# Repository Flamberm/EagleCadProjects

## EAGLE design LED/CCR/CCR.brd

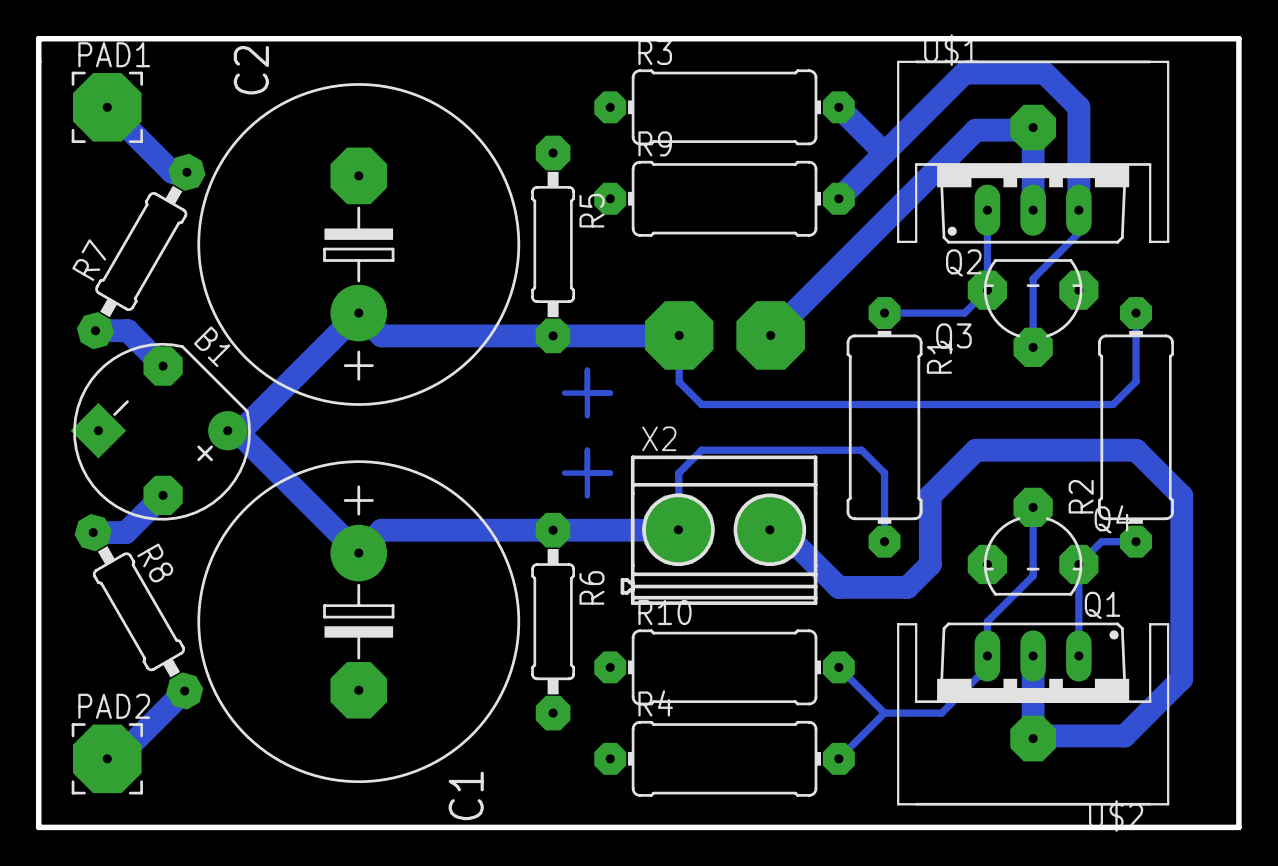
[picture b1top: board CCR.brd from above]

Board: 2 copper layers, 66.7 x 43.8 mm, 23 parts (1 on the bottom side), 12 nets.

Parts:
B1: RB1A
C1, C2: E7,5-18
PAD1, PAD2: 3,81/1,4
Q1, Q2: BUZ11BV; TO220BV
Q3, Q4: KSP42TA; SOT-92WIDE
R1, R2: 300k; 0411/12
R3, R4: 13R; 0411/12
R5, R6: 160k; 0207/10
R7, R8: NTC; 0207/10
R9, R10: 8R2; 0411/12
U$1, U$2: SK95-3M3
X1, X2: MKDSN1,5/2-5,08

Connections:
GND: B1.-, C1.-, C2.-, Q3.E, Q4.E, R3.1, R4.1, R5.1, R6.2, R9.1, R10.1
unnamed: Q1.S, Q4.B, R4.2, R10.2
unnamed: Q1.D, U$2.P$1, X2.2
unnamed: Q2.D, U$1.P$1, X1.1
unnamed: Q2.S, Q3.B, R3.2, R9.2
unnamed: Q1.G, Q4.C, R2.1
unnamed: Q2.G, Q3.C, R1.1
unnamed: PAD1.1, R7.2
unnamed: B1.AC1, R8.1
unnamed: PAD2.1, R8.2
unnamed: B1.AC2, R7.1
unnamed: B1.+, C1.+, C2.+, R1.2, R2.2, R5.2, R6.1, X1.2, X2.1

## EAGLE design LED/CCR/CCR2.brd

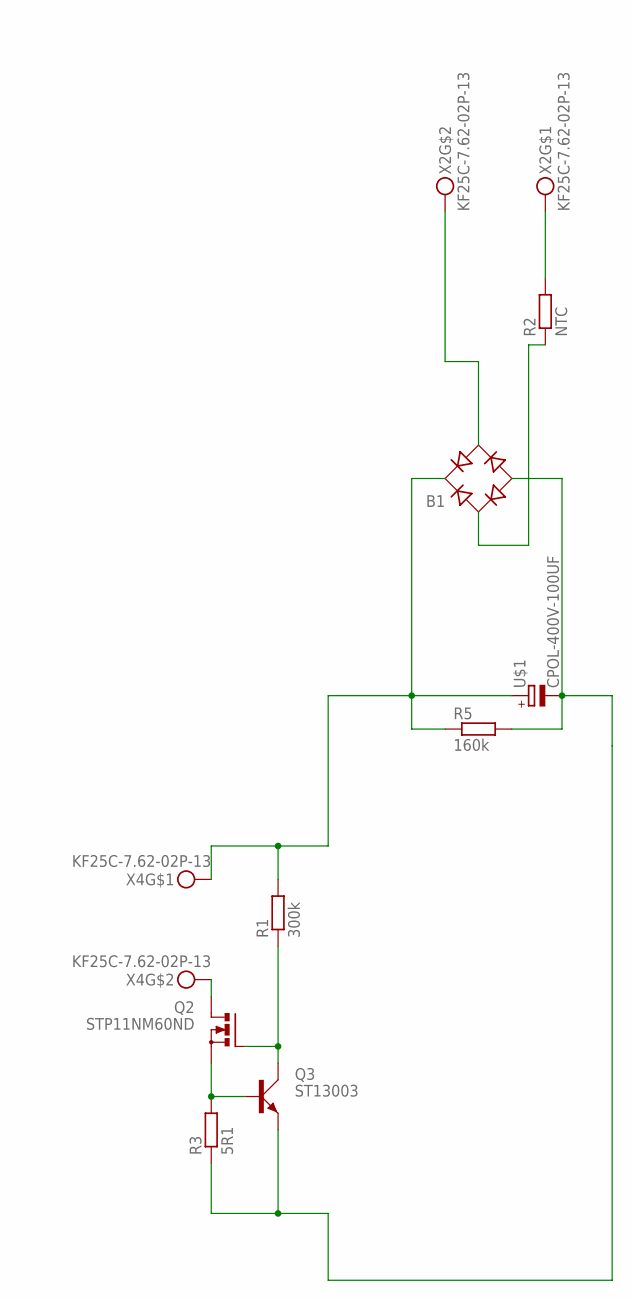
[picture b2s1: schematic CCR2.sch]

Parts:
B1: RB1A
Q2: STP11NM60ND; TO220BV
Q3: ST13003; SOT-92WIDE
R1: 300k; 0411/12
R2: NTC; 0309/10
R3: 5R1; R0805
R5: 160k; 0204/7
U$1: CPOL-400V-100UF; 18*36.5_7.62
X2, X4: KF25C-7.62-02P-13

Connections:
unnamed: B1.+, R1.2, R5.1, U$1.P$2 (+), X4.P$1
unnamed: B1.AC1, R2.1
unnamed: R2.2, X2.P$1
unnamed: B1.AC2, X2.P$2
unnamed: Q2.D, X4.P$2
unnamed: Q2.S, Q3.B, R3.2
unnamed: Q2.G, Q3.C, R1.1
unnamed: B1.-, Q3.E, R3.1, R5.2, U$1.P$1 (-)

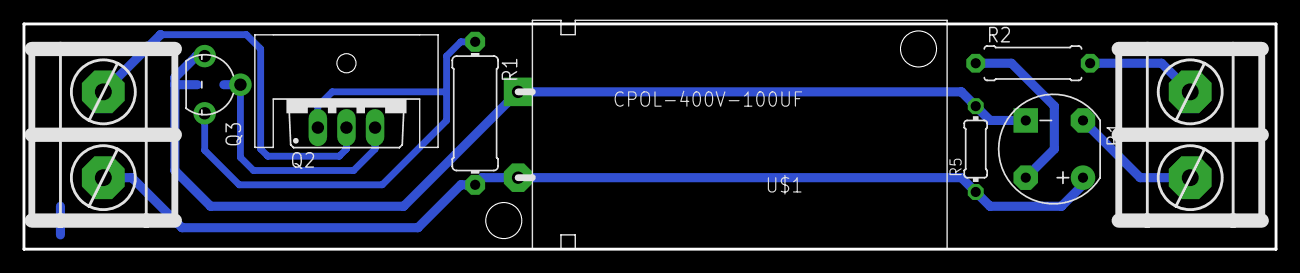
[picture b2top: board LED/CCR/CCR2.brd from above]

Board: 2 copper layers, 111.2 x 20.0 mm, 11 parts (1 on the bottom side), 8 nets.

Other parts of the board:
U$2: SK95-3M3_HOLE

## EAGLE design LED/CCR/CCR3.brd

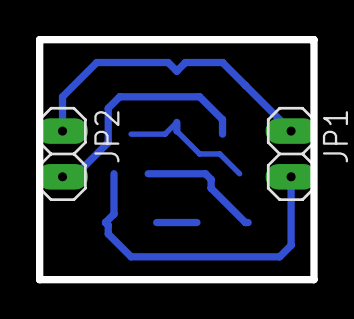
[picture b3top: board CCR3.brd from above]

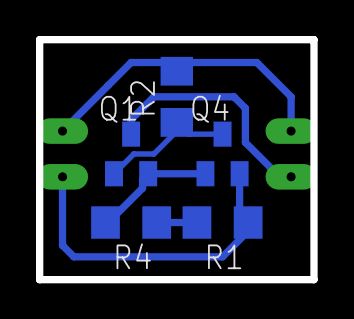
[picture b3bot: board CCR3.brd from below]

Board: 2 copper layers, 15.2 x 13.3 mm, 7 parts (5 on the bottom side), 6 nets.

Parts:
JP1, JP2: 1X02
Q1: BSS123; SOT23
Q4: BC817-40SMD; SOT23-BEC
R1, R4: 20R; R1206
R2: 20k; R1206

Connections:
GND: JP1.2, Q4.E, R1.1
unnamed: JP1.1, JP2.1, R2.2
unnamed: Q1.2, Q4.B, R4.2
unnamed: JP2.2, Q1.3
unnamed: Q1.1, Q4.C, R2.1
unnamed: R1.2, R4.1

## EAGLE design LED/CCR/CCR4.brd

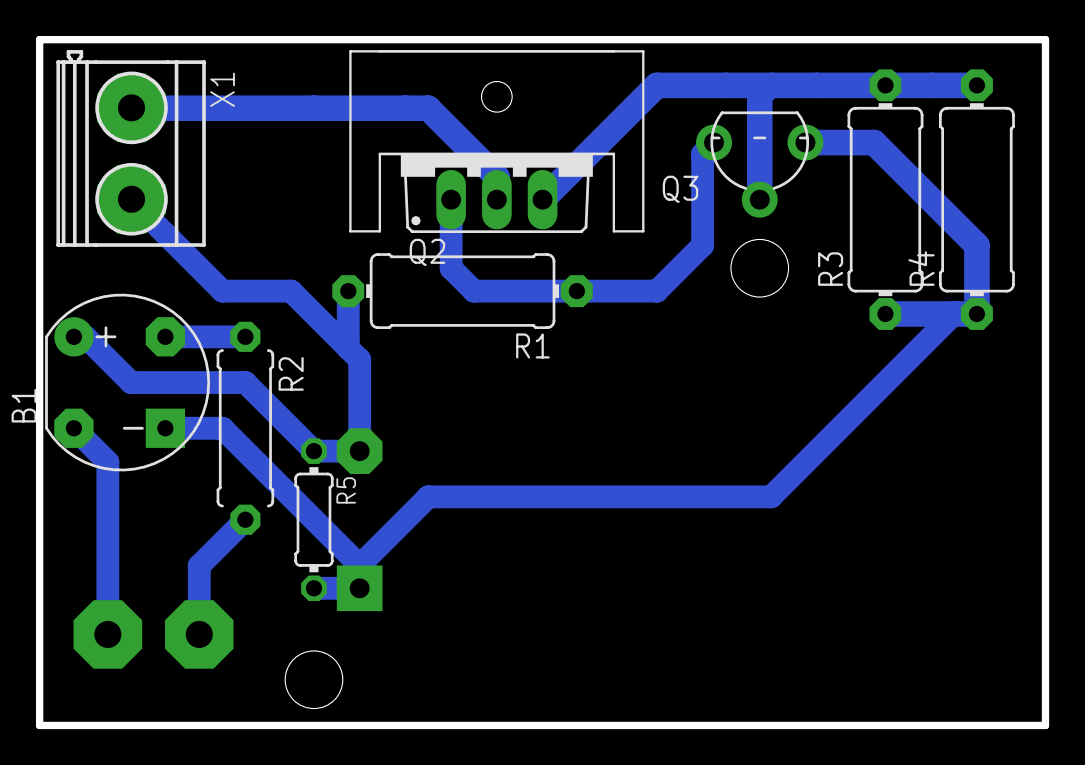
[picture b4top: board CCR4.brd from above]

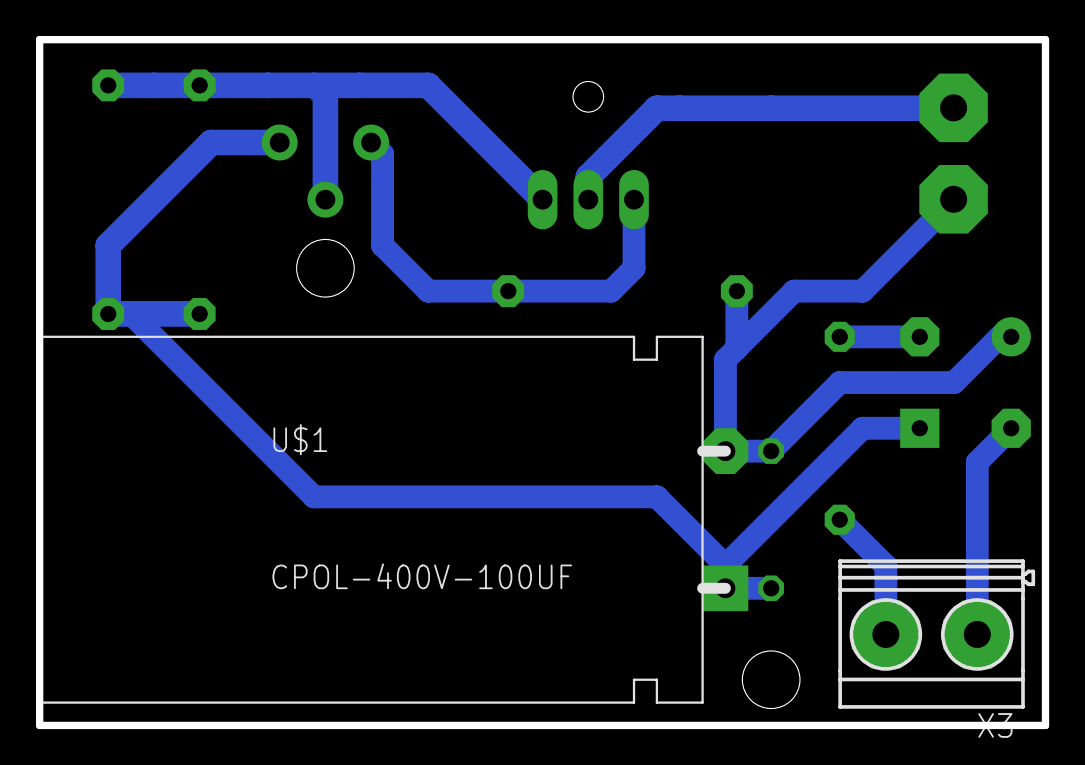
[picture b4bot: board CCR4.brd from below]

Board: 2 copper layers, 55.9 x 38.1 mm, 12 parts (2 on the bottom side), 8 nets.

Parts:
B1: RB1A
Q2: STP11NM60ND; TO220BV
Q3: ST13003; SOT-92WIDE
R1: 300k; 0411/12
R2: NTC; 0309/10
R3: 8R2; 0411/12
R4: 13R; 0411/12
R5: 160k; 0204/7
U$1: CPOL-400V-100UF; 18*36.5_7.62
U$2: SK95-3M3_HOLE
X1, X3: MKDSN1,5/2-5,08

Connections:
unnamed: B1.+, R1.2, R5.1, U$1.P$2, X1.2
unnamed: B1.AC1, R2.1
unnamed: R2.2, X3.2
unnamed: B1.AC2, X3.1
unnamed: Q2.D, X1.1
unnamed: Q2.S, Q3.B, R3.2, R4.2
unnamed: Q2.G, Q3.C, R1.1
unnamed: B1.-, Q3.E, R3.1, R4.1, R5.2, U$1.P$1

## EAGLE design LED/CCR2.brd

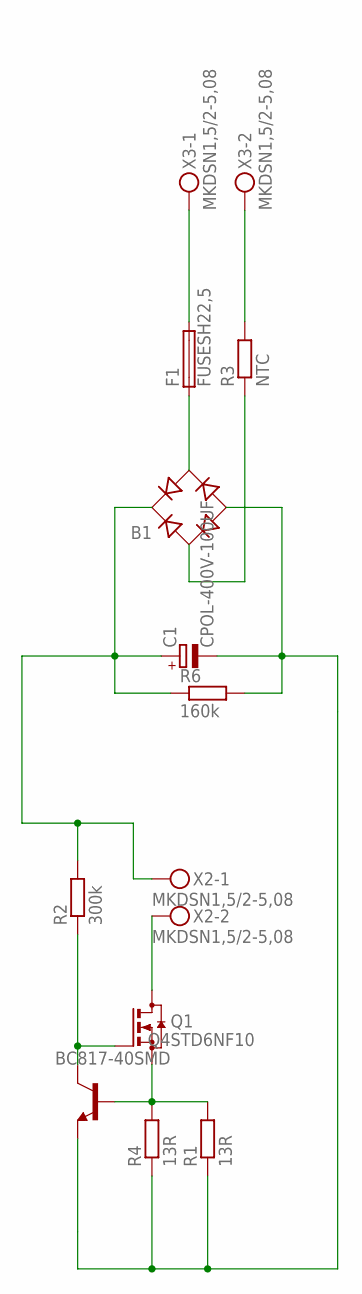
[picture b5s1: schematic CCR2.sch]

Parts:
B1: RB1A
C1: CPOL-400V-100UF; 18*36.5_7.62
F1: FUSESH22,5; SH22,5
Q1: STD6NF10; DPAK
Q4: BC817-40SMD; SOT23-BEC
R1, R4: 13R; 0411/12
R2: 300k; 0411/12
R3: NTC; 0309/10
R6: 160k; 0204/7
X2, X3: MKDSN1,5/2-5,08

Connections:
GND: B1.-, C1.P$1 (-), Q4.E, R1.1, R4.1, R6.2
unnamed: B1.+, C1.P$2 (+), R2.2, R6.1, X2.1
unnamed: R3.2, X3.2
unnamed: Q1.S, Q4.B, R1.2, R4.2
unnamed: Q1.D, X2.2
unnamed: F1.2, X3.1
unnamed: B1.AC2, F1.1
unnamed: Q1.G, Q4.C, R2.1
unnamed: B1.AC1, R3.1

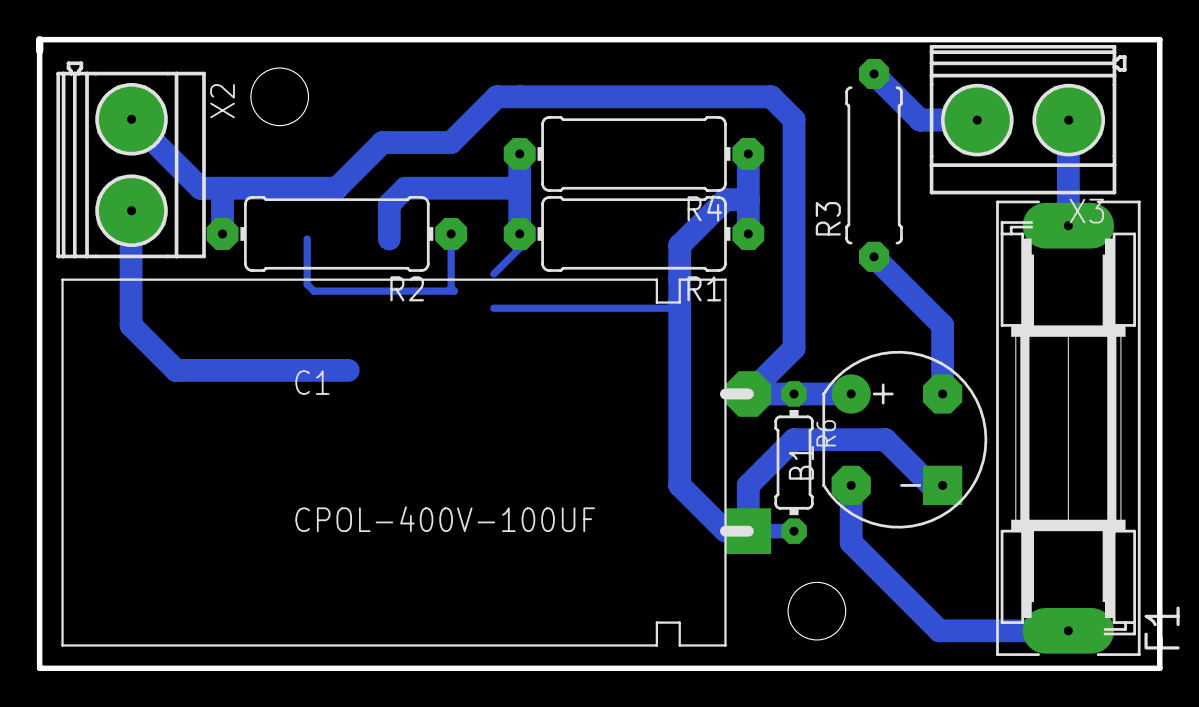
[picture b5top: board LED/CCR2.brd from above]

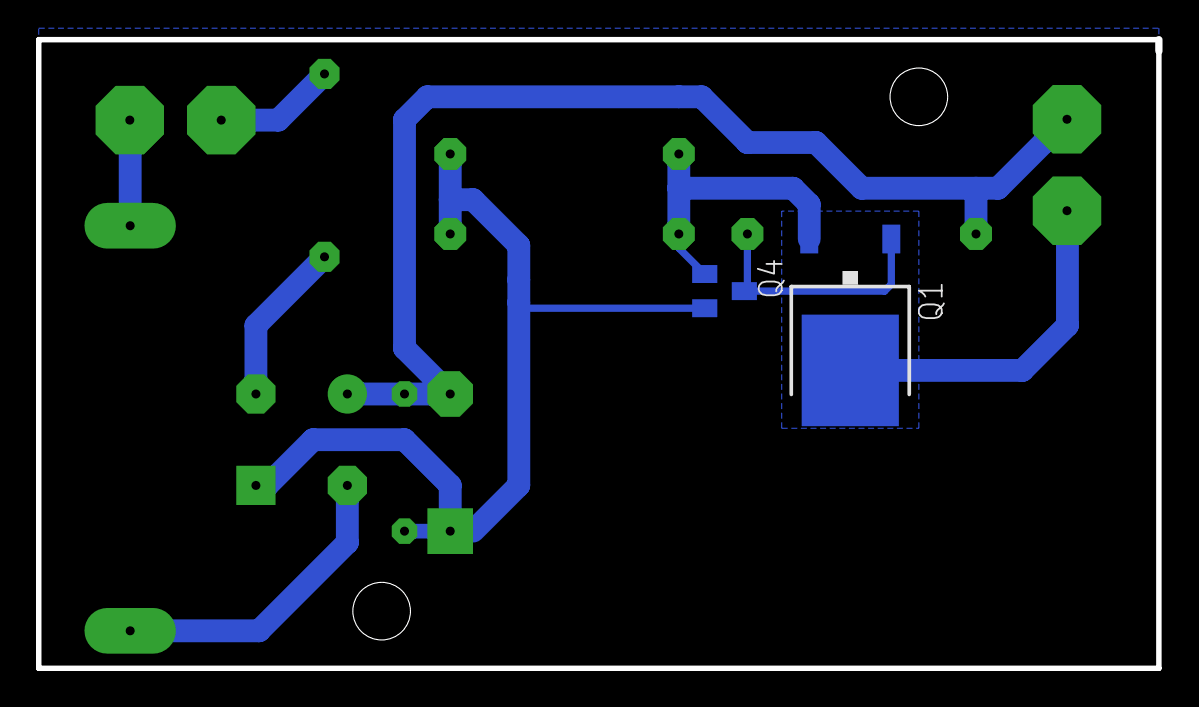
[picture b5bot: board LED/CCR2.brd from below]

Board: 2 copper layers, 62.2 x 34.9 mm, 12 parts (2 on the bottom side), 9 nets.

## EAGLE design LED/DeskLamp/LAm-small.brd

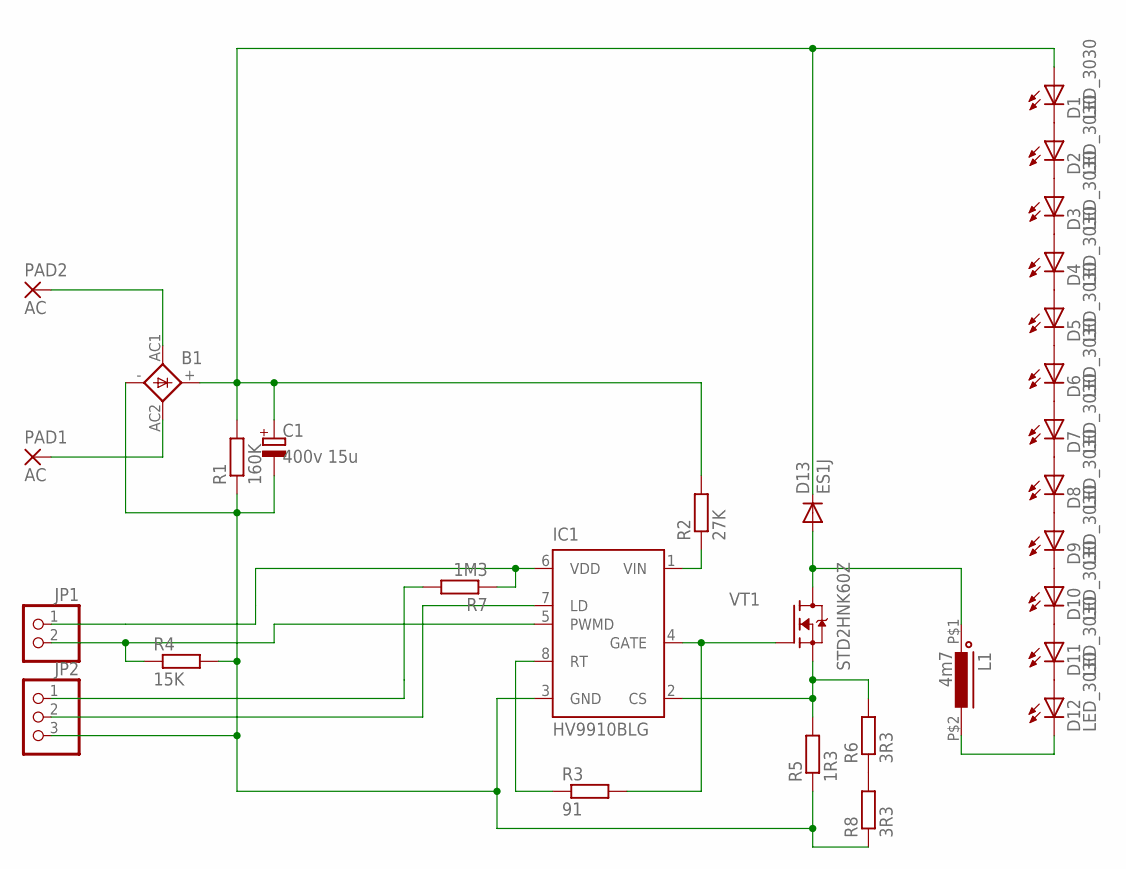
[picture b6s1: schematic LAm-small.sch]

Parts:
B1: BRIDGERB1A; RB1A
C1: 400v 15u; E7,5-16-32-HORIZ
D1, D2, D3, D4, D5, D6, D7, D8, D9, D10, D11, D12: LED_3030; LED3030
D13: ES1J; DO214AC
IC1: HV9910BLG; SOIC-08LG
JP1: PINHD-1X2/90; 1X02/90
JP2: PINHD-1X3/90; 1X03/90
L1: 4m7; SL1016
PAD1, PAD2: AC; 3,81/1,4
R1: 160K; MF-0125
R2: 27K; MF-2
R3: 91; R0805
R4: 15K; R0805
R5: 1R3; KNP-100B
R6, R8: 3R3; R0805
R7: 1M3; R0805
VT1: STD2HNK60Z; DPAK

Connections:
unnamed: D1.P$2 (C), D2.P$1 (A)
unnamed: D2.P$2 (C), D3.P$1 (A)
unnamed: D3.P$2 (C), D4.P$1 (A)
unnamed: D4.P$2 (C), D5.P$1 (A)
unnamed: D5.P$2 (C), D6.P$1 (A)
unnamed: D6.P$2 (C), D7.P$1 (A)
unnamed: D7.P$2 (C), D8.P$1 (A)
unnamed: D8.P$2 (C), D9.P$1 (A)
unnamed: D9.P$2 (C), D10.P$1 (A)
unnamed: D10.P$2 (C), D11.P$1 (A)
unnamed: D11.P$2 (C), D12.P$1 (A)
unnamed: B1.AC1, PAD2.1
unnamed: B1.AC2, PAD1.1
unnamed: B1.-, C1.-, IC1.3 (GND), JP2.3, R1.1, R4.2, R5.1, R8.1
unnamed: R6.1, R8.2
unnamed: B1.+, C1.+, D1.P$1 (A), D13.C, R1.2, R2.2
unnamed: IC1.1 (VIN), R2.1
unnamed: IC1.2 (CS), R5.2, R6.2, VT1.S
unnamed: IC1.8 (RT), R3.1
unnamed: IC1.4 (GATE), R3.2, VT1.G
unnamed: D12.P$2 (C), L1.P$2 (2)
unnamed: D13.A, L1.P$1 (1), VT1.D
unnamed: IC1.5 (PWMD), JP1.2, R4.1
unnamed: IC1.6 (VDD), JP1.1, R7.1
unnamed: JP2.1, R7.2
unnamed: IC1.7 (LD), JP2.2

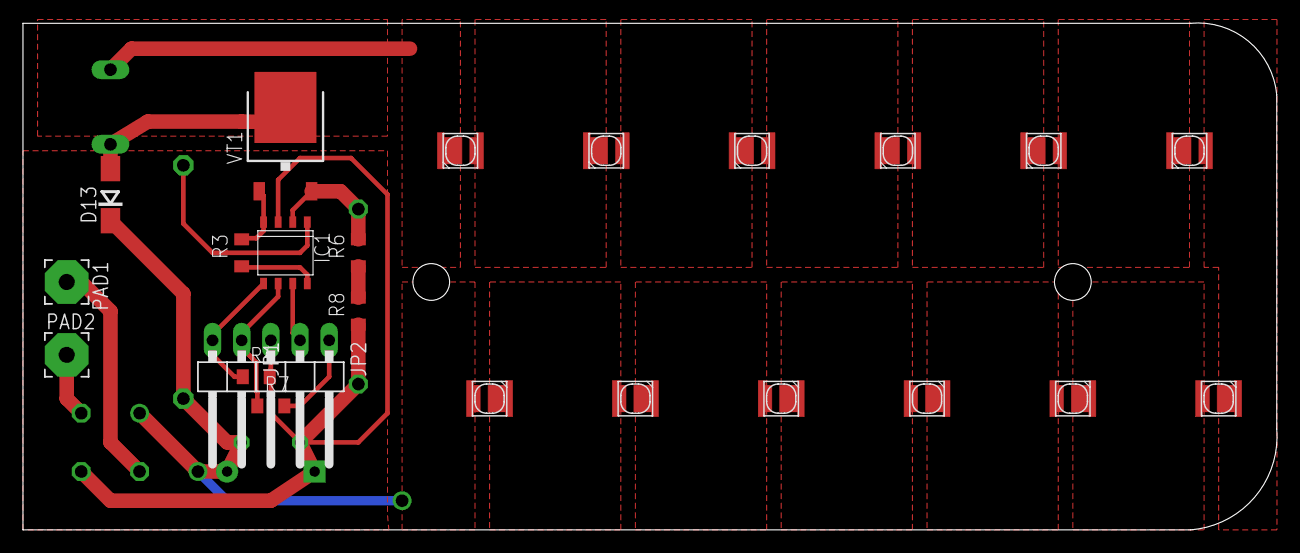
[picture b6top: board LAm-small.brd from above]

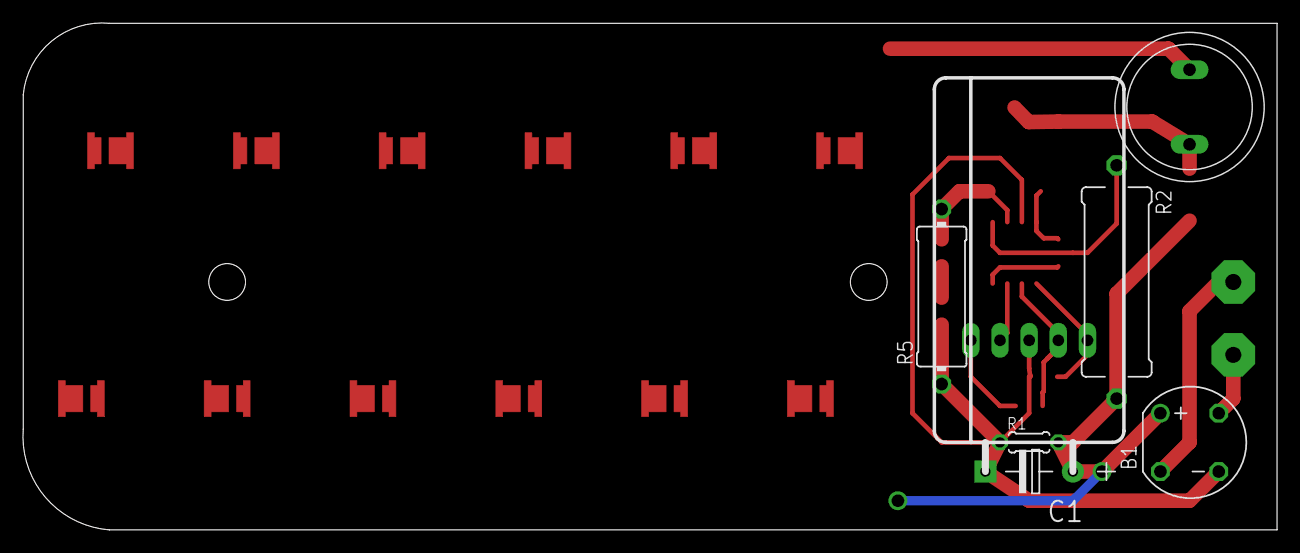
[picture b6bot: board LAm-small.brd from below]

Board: 2 copper layers, 109.2 x 44.1 mm, 30 parts (6 on the bottom side), 26 nets.
